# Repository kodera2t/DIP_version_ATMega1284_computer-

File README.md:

# DIP_version_ATMega1284_computer-
initial

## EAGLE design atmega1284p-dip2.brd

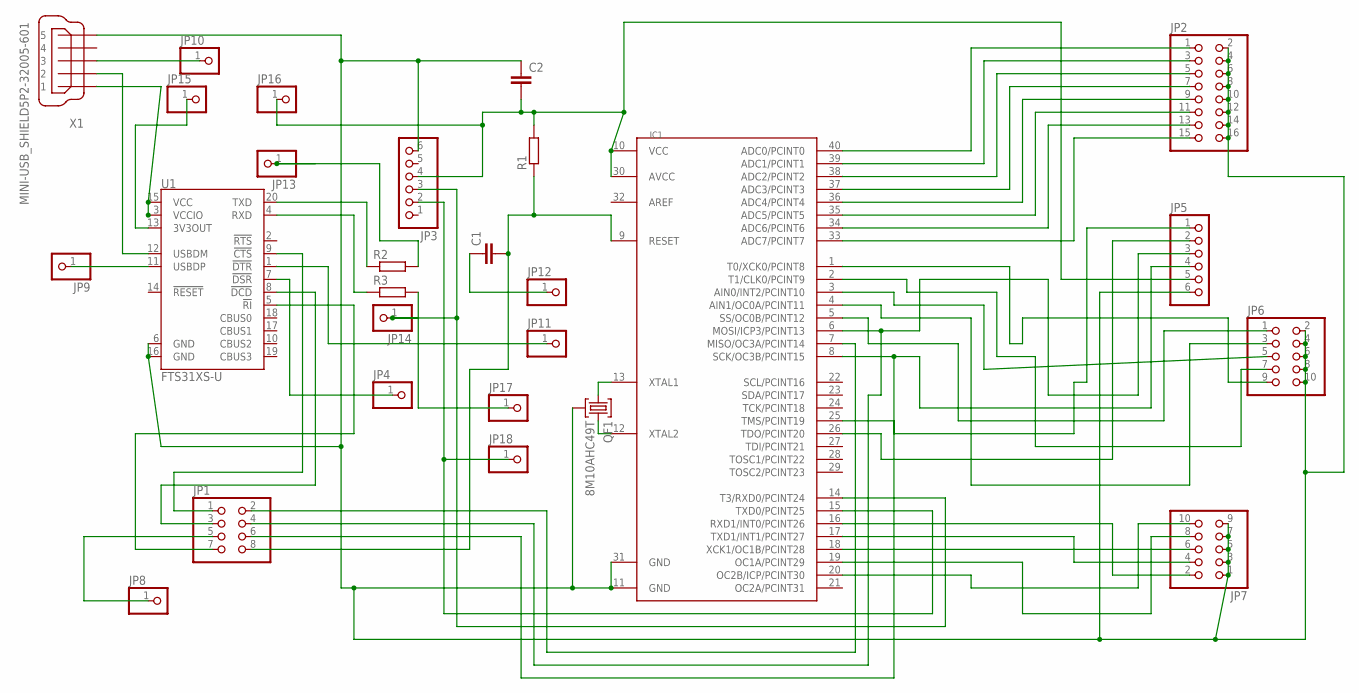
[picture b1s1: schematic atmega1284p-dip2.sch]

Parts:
C1, C2: C-EUC0805; C0805
IC1: MEGA1284P; DIL40
JP1: PINHD-2X4; 2X04
JP2: PINHD-2X8; 2X08
JP3, JP5: PINHD-1X6; 1X06
JP4, JP8, JP9, JP10, JP11, JP12, JP13, JP14, JP15, JP16, JP17, JP18: PINHD-1X1; 1X01
JP6, JP7: PINHD-2X5; 2X05
QF1: 8M10AHC49T; HC49U
R1: R-EU_R0805; R0805
R2, R3: RR0603; R0603
U1: FTS31XS-U; SSOP20_L
X1: MINI-USB_SHIELD5P2-32005-601; 32005-601

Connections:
unnamed: IC1.40 (ADC0/PCINT0), JP2.1
unnamed: IC1.39 (ADC1/PCINT1), JP2.3
unnamed: IC1.6 (MOSI/ICP3/PCINT13), JP1.4, JP5.3
unnamed: C2.1, IC1.11 (GND), IC1.31 (GND), JP2.2, JP2.4, JP2.6, JP2.8, JP2.10, JP2.12, JP2.14, JP2.16, JP3.6, JP5.6, JP6.2, JP6.4, JP6.6, JP6.8, JP6.10, JP7.1, JP7.3, JP7.5, JP7.7, JP7.9, QF1.2, U1.6 (GND), U1.16 (GND), X1.5
unnamed: IC1.13 (XTAL1), QF1.1
unnamed: IC1.12 (XTAL2), QF1.3
unnamed: U1.3 (VCCIO), U1.15 (VCC), X1.1
unnamed: IC1.8 (SCK/OC3B/PCINT15), JP1.6, JP5.4
unnamed: IC1.16 (RXD1/INT0/PCINT26), JP7.2
unnamed: C1.2, IC1.9 (RESET), JP1.8, R1.1
unnamed: JP11.1, U1.1 (!DTR)
unnamed: IC1.15 (TXD0/PCINT25), JP3.2, JP18.1
unnamed: IC1.14 (T3/RXD0/PCINT24), JP3.3, JP14.1
unnamed: IC1.25 (TMS/PCINT19), JP5.1
unnamed: IC1.26 (TDO/PCINT20), JP5.2
unnamed: IC1.17 (TXD1/INT1/PCINT27), JP7.4
unnamed: IC1.38 (ADC2/PCINT2), JP2.5
unnamed: IC1.37 (ADC3/PCINT3), JP2.7
unnamed: IC1.36 (ADC4/PCINT4), JP2.9
unnamed: IC1.35 (ADC5/PCINT5), JP2.11
unnamed: IC1.34 (ADC6/PCINT6), JP2.13
unnamed: IC1.33 (ADC7/PCINT7), JP2.15
unnamed: IC1.1 (T0/XCK0/PCINT8), JP6.9
unnamed: IC1.2 (T1/CLK0/PCINT9), JP6.7
unnamed: IC1.3 (AIN0/INT2/PCINT10), JP6.5
unnamed: IC1.4 (AIN1/OC0A/PCINT11), JP6.3
unnamed: IC1.5 (SS/OC0B/PCINT12), JP6.1
unnamed: IC1.18 (XCK1/OC1B/PCINT28), JP7.6
unnamed: IC1.19 (OC1A/PCINT29), JP7.8
unnamed: IC1.20 (OC2B/ICP/PCINT30), JP7.10
unnamed: IC1.7 (MISO/OC3A/PCINT14), JP1.2
unnamed: C2.2, IC1.10 (VCC), IC1.30 (AVCC), JP3.4, JP5.5, JP16.1, R1.2
unnamed: U1.12 (USBDM), X1.2
unnamed: JP9.1, U1.11 (USBDP)
unnamed: R2.1, U1.20 (TXD)
unnamed: R3.1, U1.4 (RXD)
unnamed: JP4.1, U1.7 (!DSR)
unnamed: JP1.1, U1.9 (!CTS)
unnamed: JP1.3, U1.8 (!DCD)
unnamed: JP1.5, JP8.1
unnamed: JP1.7, U1.5 (!RI)
unnamed: JP10.1, X1.3
unnamed: C1.1, JP12.1
unnamed: JP13.1, R2.2
unnamed: JP15.1, U1.13 (3V3OUT)
unnamed: JP17.1, R3.2

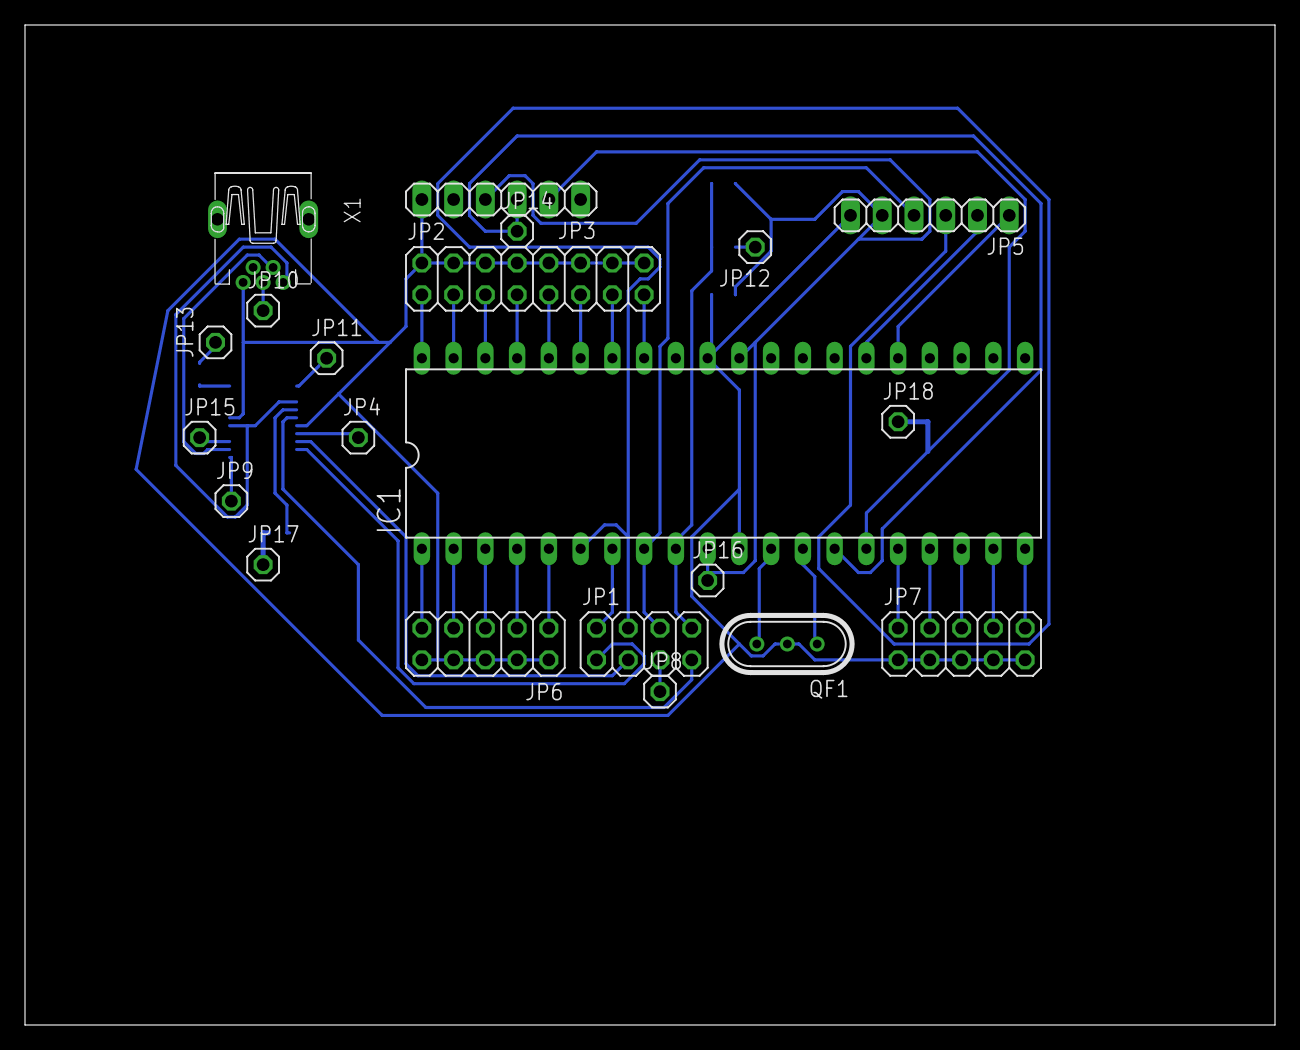
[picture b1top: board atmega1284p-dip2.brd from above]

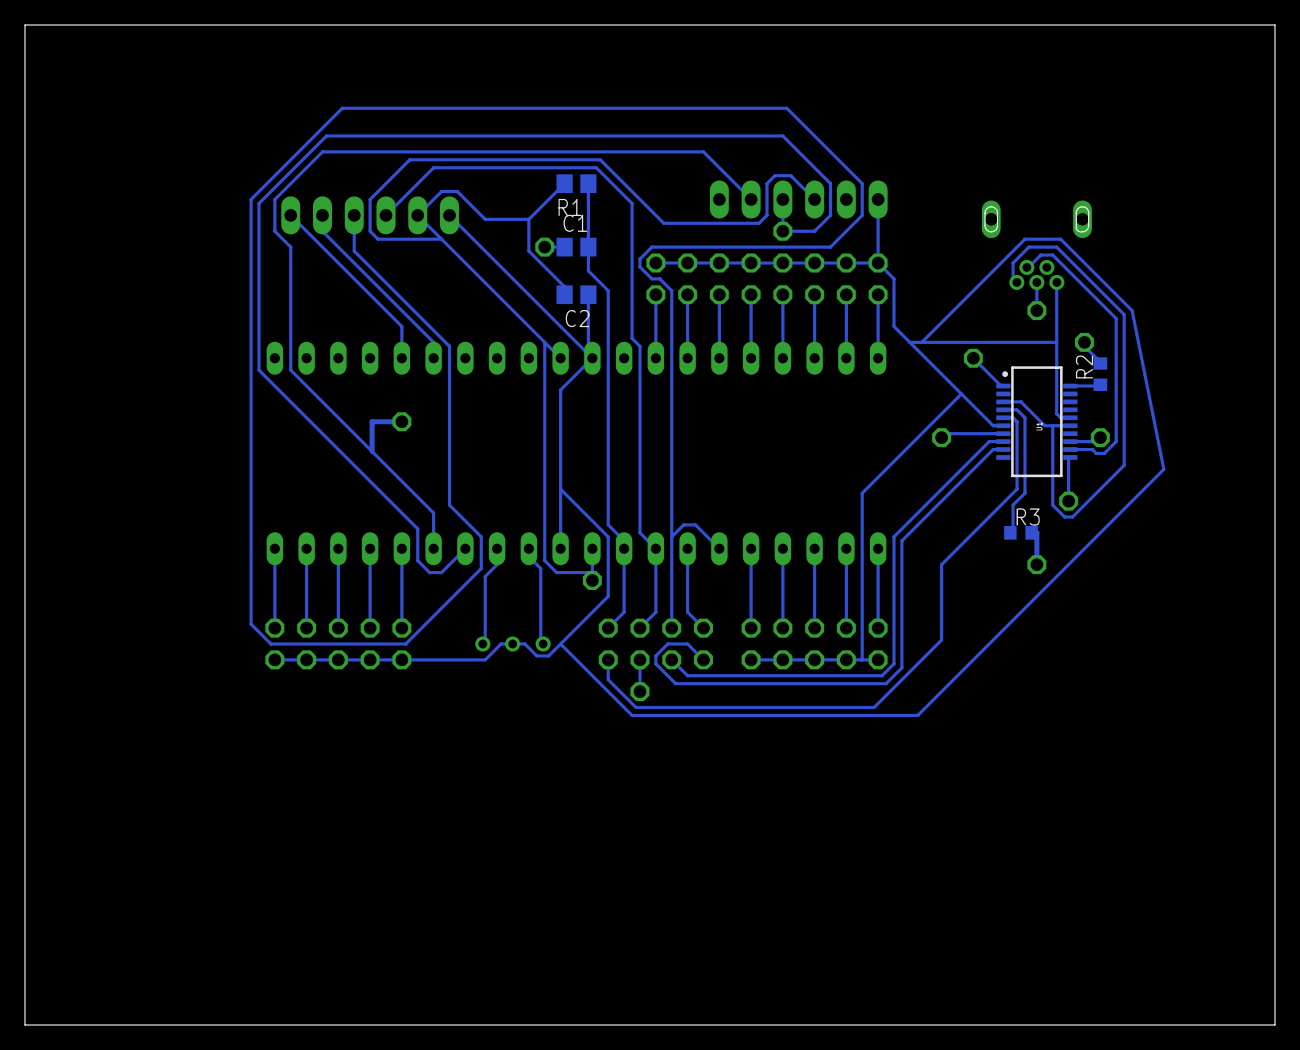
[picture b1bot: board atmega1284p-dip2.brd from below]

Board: 2 copper layers, 100.0 x 80.0 mm, 27 parts (6 on the bottom side), 46 nets.

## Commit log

2015-02-18 initial
    initial
2015-02-24 gerber and drill datas

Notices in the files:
parts and their libraries:
SparkFun-DigitalIC: Licensing: Creative Commons ShareAlike 4.0 International - https://creativecommons.org/licenses/by-sa/4.0
